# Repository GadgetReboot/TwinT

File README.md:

# TwinT
<BR><BR><BR>
Twin T Filter/Oscillator PCB for experimentation

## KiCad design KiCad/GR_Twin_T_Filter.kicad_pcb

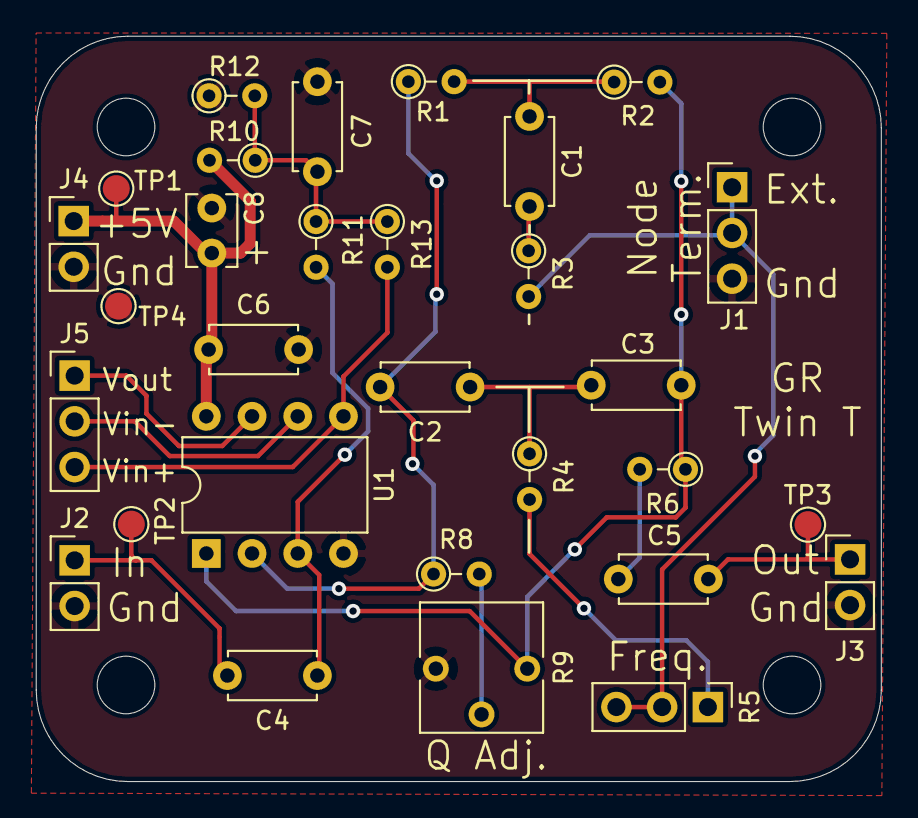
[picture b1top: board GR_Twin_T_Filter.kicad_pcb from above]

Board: 2 copper layers, 46.9 x 41.4 mm, 34 parts (0 on the bottom side), 18 nets.

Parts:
C1: 6n8; C_Disc_D4.7mm_W2.5mm_P5.00mm
C2: 10n; C_Disc_D4.7mm_W2.5mm_P5.00mm
C3: 22n; C_Disc_D4.7mm_W2.5mm_P5.00mm
C4, C5: 680nF; C_Disc_D4.7mm_W2.5mm_P5.00mm
C6, C7: 100nF; C_Disc_D4.7mm_W2.5mm_P5.00mm
C8: 4.7uF; C_Disc_D3.8mm_W2.6mm_P2.50mm
J1, J5: Conn_01x03; PinHeader_1x03_P2.54mm_Vertical
J2, J3, J4: Conn_01x02; PinHeader_1x02_P2.54mm_Vertical
MH1, MH2, MH3, MH4: MountingHole; MountingHole_3.2mm_M3
R1, R2: 18K; R_Axial_DIN0204_L3.6mm_D1.6mm_P2.54mm_Vertical
R3: 180K; R_Axial_DIN0204_L3.6mm_D1.6mm_P2.54mm_Vertical
R4: 680; R_Axial_DIN0204_L3.6mm_D1.6mm_P2.54mm_Vertical
R5: 10K; PinHeader_1x03_P2.54mm_Vertical
R6: 100r; R_Axial_DIN0204_L3.6mm_D1.6mm_P2.54mm_Vertical
R8: 100K; R_Axial_DIN0204_L3.6mm_D1.6mm_P2.54mm_Vertical
R9: 10K; Potentiometer_Vishay_T73YP_Vertical
R10: 10K; R_Axial_DIN0204_L3.6mm_D1.6mm_P2.54mm_Vertical
R11, R13: 1M; R_Axial_DIN0204_L3.6mm_D1.6mm_P2.54mm_Vertical
R12: 4K3; R_Axial_DIN0204_L3.6mm_D1.6mm_P2.54mm_Vertical
TP1, TP2, TP3, TP4: TestPoint; TestPoint_Pad_D1.5mm
U1: LM358; DIP-8_W7.62mm

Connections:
+5V: C6.1, C8.1, J4.1, R10.2, TP1.1, U1.8
/Ext.Use: J1.1, J1.2, R3.2, R5.2, R5.3
/In: C4.2, J2.1, TP2.1
/Out: C5.1, J3.1, TP3.1
/Vbias: C7.1, R10.1, R11.1, R12.2, R13.1
/Vin+: J5.3, R13.2, U1.5
/Vin-: J5.2, U1.6
/Vout: J5.1, U1.7
GNDREF: C6.2, C7.2, C8.2, J1.3, J2.2, J3.2, J4.2, R9.1, R12.1, TP4.1, U1.4
unnamed: C1.1, R3.1
unnamed: C1.2, R1.2, R2.1
unnamed: C2.1, C3.2, R4.1
unnamed: C2.2, R1.1, R8.1, U1.2
unnamed: C3.1, R2.2, R6.1, R9.3, U1.1
unnamed: C4.1, R11.2, U1.3
unnamed: C5.2, R6.2
unnamed: R4.2, R5.1
unnamed: R8.2, R9.2
